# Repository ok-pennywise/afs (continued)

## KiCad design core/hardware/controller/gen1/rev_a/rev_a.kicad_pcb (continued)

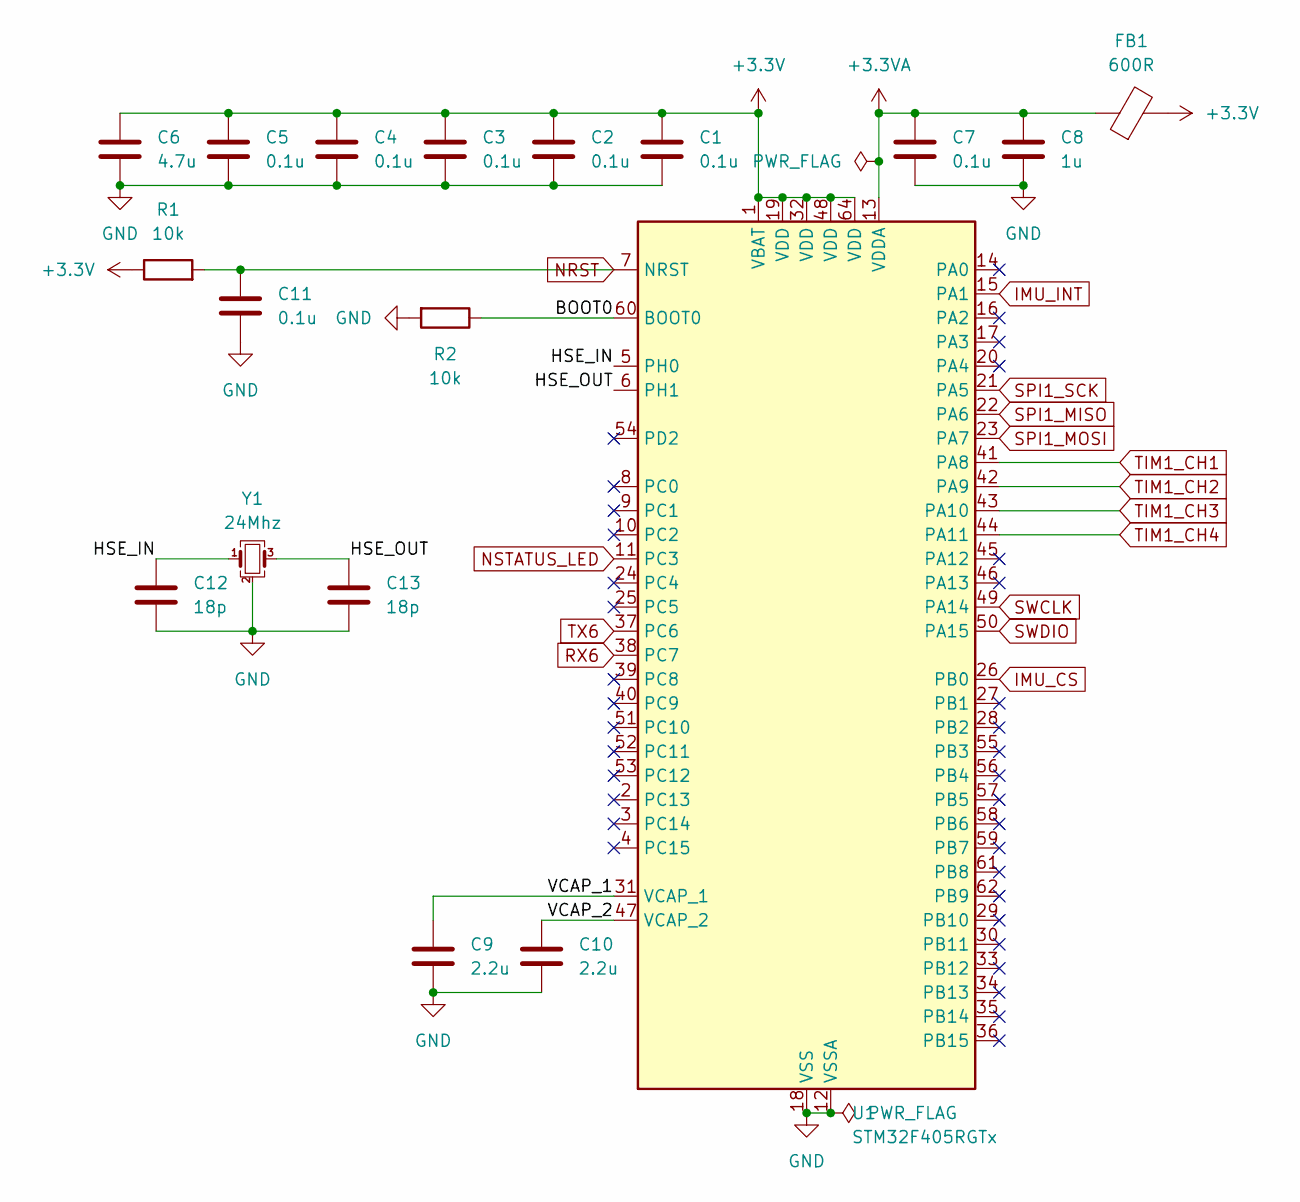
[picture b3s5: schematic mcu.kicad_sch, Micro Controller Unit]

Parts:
C1, C2, C3, C4, C5, C7, C11: 0.1u; C_0603_1608Metric_Pad1.08x0.95mm_HandSolder
C6: 4.7u; C_0603_1608Metric_Pad1.08x0.95mm_HandSolder
C8: 1u; C_0603_1608Metric_Pad1.08x0.95mm_HandSolder
C9, C10: 2.2u; C_0603_1608Metric_Pad1.08x0.95mm_HandSolder
C12, C13: 18p; C_0805_2012Metric_Pad1.18x1.45mm_HandSolder
FB1: 600R; L_0603_1608Metric_Pad1.05x0.95mm_HandSolder
R1, R2: 10k; R_0603_1608Metric_Pad0.98x0.95mm_HandSolder
U1: STM32F405RGTx; LQFP-64_10x10mm_P0.5mm
Y1: 24Mhz; Crystal_SMD_Abracon_ABM8G-4Pin_3.2x2.5mm

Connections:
+3.3V: C1.1, C2.1, C3.1, C4.1, C5.1, C6.1, FB1.2, R1.1, U1.1 (VBAT), U1.19 (VDD), U1.32 (VDD), U1.48 (VDD), U1.64 (VDD); also elsewhere on the board
+3.3VA: C7.1, C8.1, FB1.1, U1.13 (VDDA)
/MCU/BOOT0: R2.1, U1.60 (BOOT0)
/MCU/HSE_IN: C12.1, U1.5 (PH0), Y1.1
/MCU/HSE_OUT: C13.1, U1.6 (PH1), Y1.3
/MCU/VCAP_1: C9.1, U1.31 (VCAP_1)
/MCU/VCAP_2: C10.1, U1.47 (VCAP_2)
GND: C1.2, C2.2, C3.2, C4.2, C5.2, C6.2, C7.2, C8.2, C9.2, C10.2, C11.2, C12.2, C13.2, R2.2, U1.12 (VSSA), U1.18 (VSS), U1.63 (VSS), Y1.2 (G), Y1.4 (G); also elsewhere on the board
IMU_CS: U1.26 (PB0); also elsewhere on the board
IMU_INT: U1.15 (PA1); also elsewhere on the board
NRST: C11.1, R1.2, U1.7 (NRST); also elsewhere on the board
NSTATUS_LED: U1.11 (PC3); also elsewhere on the board
RX6: U1.38 (PC7); also elsewhere on the board
SPI1_MISO: U1.22 (PA6); also elsewhere on the board
SPI1_MOSI: U1.23 (PA7); also elsewhere on the board
SPI1_SCK: U1.21 (PA5); also elsewhere on the board
SWCLK: U1.49 (PA14); also elsewhere on the board
SWDIO: U1.50 (PA15); also elsewhere on the board
TIM1_CH1: U1.41 (PA8); also elsewhere on the board
TIM1_CH2: U1.42 (PA9); also elsewhere on the board
TIM1_CH3: U1.43 (PA10); also elsewhere on the board
TIM1_CH4: U1.44 (PA11); also elsewhere on the board
TX6: U1.37 (PC6); also elsewhere on the board

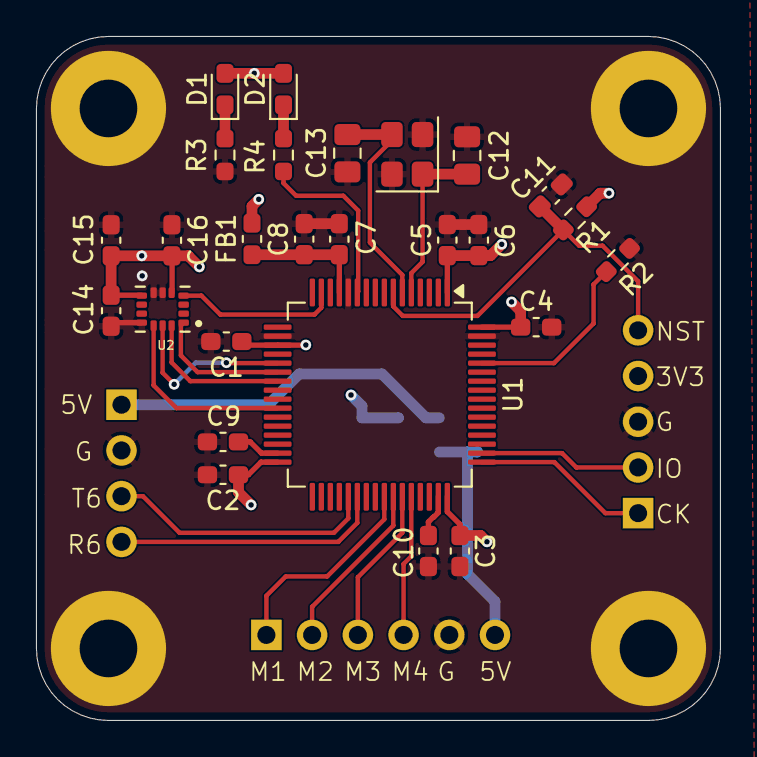
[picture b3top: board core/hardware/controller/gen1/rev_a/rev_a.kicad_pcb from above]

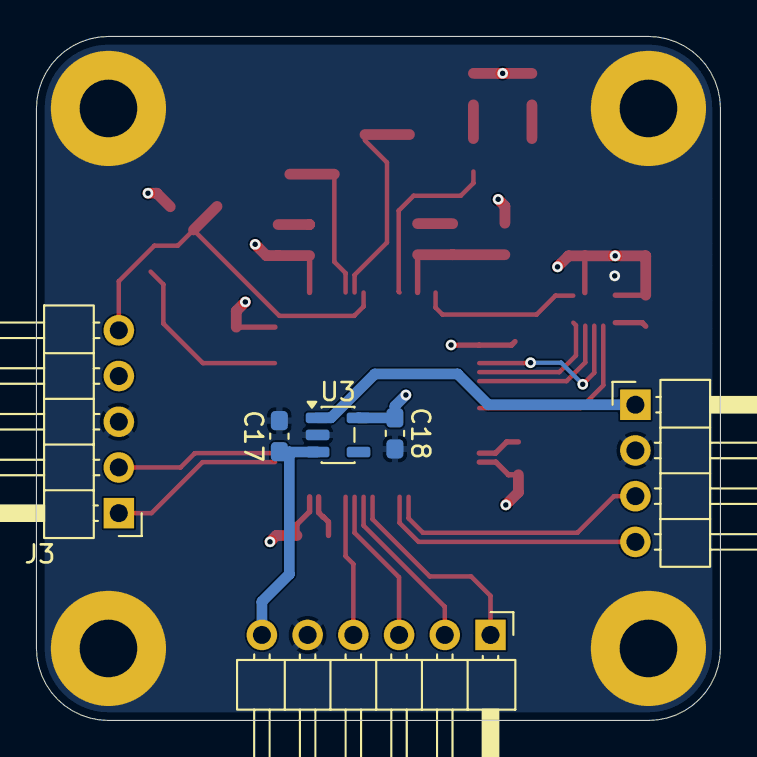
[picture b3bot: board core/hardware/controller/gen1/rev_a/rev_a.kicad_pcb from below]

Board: 4 copper layers, 38.0 x 38.0 mm, 36 parts (6 on the bottom side), 26 nets.

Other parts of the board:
H1, H2, H3, H4: MountingHole_Pad; MountingHole_3.2mm_M3_Pad

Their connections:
GND: H1.1 (1_1), H2.1 (1_1), H3.1 (1_1), H4.1 (1_1); also elsewhere on the board

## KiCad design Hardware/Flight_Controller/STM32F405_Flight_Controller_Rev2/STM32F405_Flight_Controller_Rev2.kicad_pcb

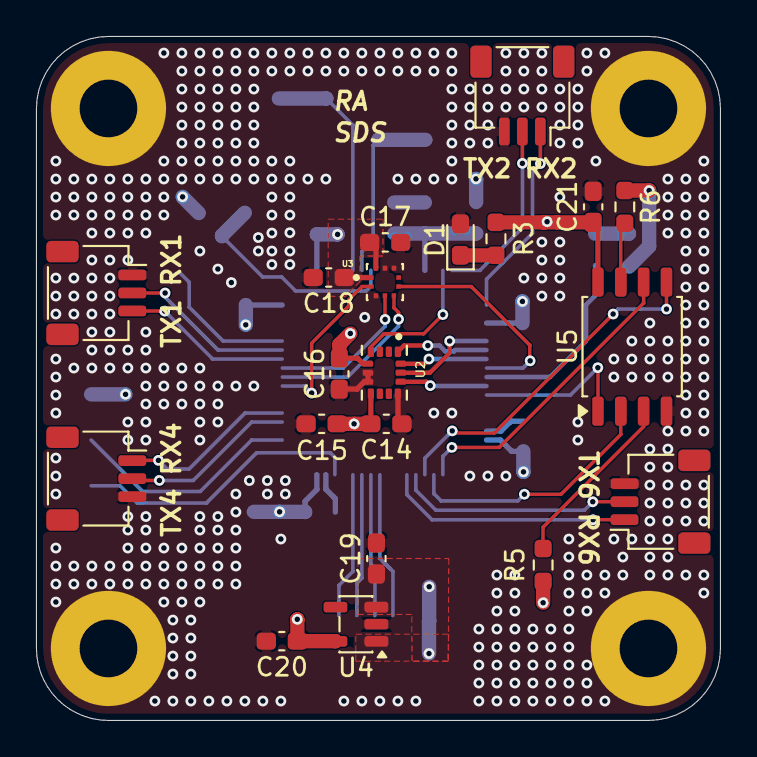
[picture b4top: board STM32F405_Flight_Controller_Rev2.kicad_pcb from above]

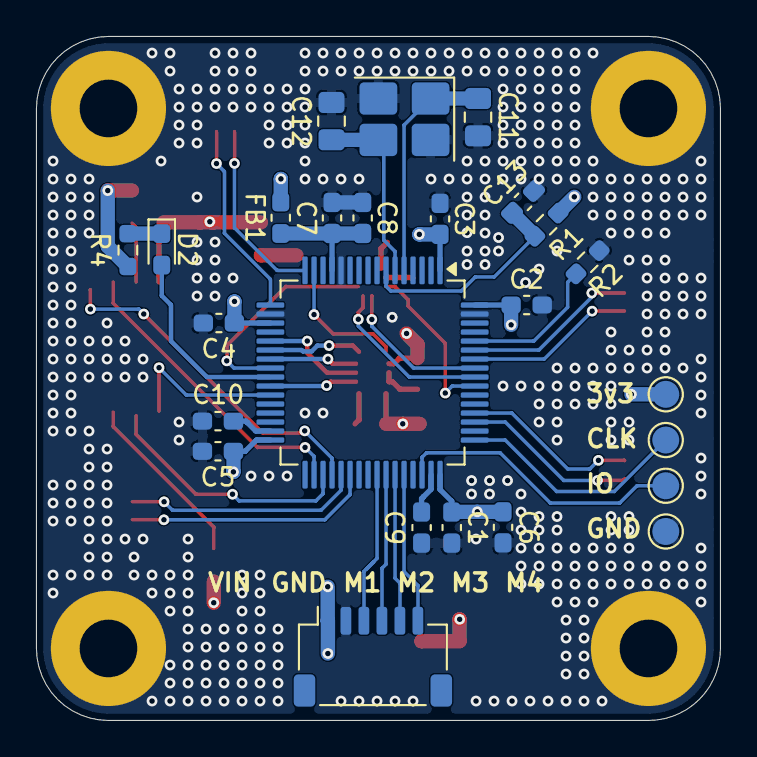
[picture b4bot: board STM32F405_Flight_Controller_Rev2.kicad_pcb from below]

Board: 4 copper layers, 38.0 x 38.0 mm, 49 parts (25 on the bottom side), 42 nets.

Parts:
C1, C2, C3, C4, C5, C7, C13, C14, C17, C18, C21: 0.1u; C_0603_1608Metric_Pad1.08x0.95mm_HandSolder
C6: 4.7u; C_0603_1608Metric_Pad1.08x0.95mm_HandSolder
C8, C19, C20: 1u; C_0603_1608Metric_Pad1.08x0.95mm_HandSolder
C9, C10, C15: 2.2u; C_0603_1608Metric_Pad1.08x0.95mm_HandSolder
C11, C12: 18p; C_0805_2012Metric_Pad1.18x1.45mm_HandSolder
C16: 10n; C_0603_1608Metric_Pad1.08x0.95mm_HandSolder
D1: RED; LED_0603_1608Metric_Pad1.05x0.95mm_HandSolder
D2: GREEN; LED_0603_1608Metric_Pad1.05x0.95mm_HandSolder
FB1: 600R; L_0603_1608Metric_Pad1.05x0.95mm_HandSolder
H1, H2, H3, H4: MountingHole_Pad; MountingHole_3.2mm_M3_Pad
J1: Conn_01x06_Socket; JST_SH_SM06B-SRSS-TB_1x06-1MP_P1.00mm_Horizontal
J2, J3, J4, J5: Conn_01x03_Socket; JST_SH_SM03B-SRSS-TB_1x03-1MP_P1.00mm_Horizontal
R1, R2, R5, R6: 10k; R_0603_1608Metric_Pad0.98x0.95mm_HandSolder
R3, R4: 330; R_0603_1608Metric_Pad0.98x0.95mm_HandSolder
TP1, TP2, TP3, TP4: TestPoint; TestPoint_Pad_D1.5mm
U1: STM32F405RGTx; LQFP-64_10x10mm_P0.5mm
U2: ICM-42688-P
U3: BMP390L
U4: AP2112K-3.3; SOT-23-5
U5: W25Q128JVS; SOIC-8_5.3x5.3mm_P1.27mm
Y1: Crystal; Crystal_SMD_3225-4Pin_3.2x2.5mm_HandSoldering

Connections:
+3.3V: C1.1, C2.1, C3.1, C4.1, C5.1, C6.1, C14.2, C15.2, C16.1, C17.1, C18.1, C20.1, C21.1, FB1.2, R1.1, R3.2, R4.2, R5.2, R6.1, TP1.1 (1_1), U1.1 (VBAT), U1.19 (VDD), U1.32 (VDD), U1.48 (VDD), U1.64 (VDD), U2.5 (VDDIO), U2.8 (VDD), U3.1 (VDDIO), U3.10 (VDD), U4.5 (VOUT), U5.8 (VCC)
+3.3VA: C7.1, C8.1, FB1.1, U1.13 (VDDA)
+5V: C19.1, J1.1, U4.1 (VIN), U4.3 (EN)
/MCU/BOOT0: R2.2, U1.60 (BOOT0)
/MCU/OSC_IN: C11.1, U1.5 (PH0), Y1.1
/MCU/OSC_OUT: C12.1, U1.6 (PH1), Y1.3
BARO_CS: U1.24 (PC4), U3.6 (~CS)
FLASH_CS: U1.27 (PB1), U5.1 (~CS)
GND: C1.2, C2.2, C3.2, C4.2, C5.2, C6.2, C7.2, C8.2, C9.2, C10.2, C11.2, C12.2, C13.2, C14.1, C15.1, C16.2, C17.2, C18.2, C19.2, C20.2, C21.2, D1.2 (A), H1.1 (1_1), H2.1 (1_1), H3.1 (1_1), H4.1 (1_1), J1.2, J2.1, J3.3, J4.3, J5.3, R2.1, TP4.1 (1_1), U1.12 (VSSA), U1.18 (VSS), U1.63 (VSS), U2.6 (GND), U2.7 (RESV_7), U2.11 (RESV_11), U3.3 (VSS/GND), U3.8 (VSS/GND), U3.9 (VSS/GND), U4.2 (GND), U5.4 (GND), Y1.2 (G), Y1.4 (G)
IMU_CS: U1.26 (PB0), U2.12 (AP_CS)
IMU_INT: U1.15 (PA1), U2.4 (INT1/INT)
NRST: C13.1, R1.2, U1.7 (NRST)
NSTATUS_LED: D2.2 (A), U1.25 (PC5)
unnamed: D1.1 (K), R3.1
unnamed: D2.1 (K), R4.1
unnamed: C10.1, U1.31 (VCAP_1)
unnamed: C9.1, U1.47 (VCAP_2)
unnamed: R6.2, U5.7 (~HOLD/~RESET/IO_{3})
unnamed: R5.1, U5.3 (~WP/IO_{2})
RX1: J2.2, U1.59 (PB7)
RX2: J4.1, U1.17 (PA3)
RX4: J5.1, U1.52 (PC11)
RX6: J3.1, U1.38 (PC7)
SPI1_MISO: U1.22 (PA6), U2.1 (AP_SDO/AP_AD0)
SPI1_MOSI: U1.23 (PA7), U2.14 (AP_SDA/AP_SDIO/AP_SDI)
SPI1_SCK: U1.21 (PA5), U2.13 (AP_SCL/AP_SCLK)
SPI2_MISO: U1.35 (PB14), U5.2 (DO/IO_{1})
SPI2_MOSI: U1.36 (PB15), U5.5 (DI/IO_{0})
SPI2_SCK: U1.34 (PB13), U5.6 (CLK)
SPI3_MISO: U1.56 (PB4), U3.5 (SDO/DNC/SA0)
SPI3_MOSI: U1.57 (PB5), U3.4 (SDI/SDO/SDA)
SPI3_SCK: U1.55 (PB3), U3.2 (SCK/SCL)
SWCLK: TP2.1 (1_1), U1.49 (PA14)
SWDIO: TP3.1 (1_1), U1.46 (PA13)
TIM1_CH1: J1.3, U1.41 (PA8)
TIM1_CH2: J1.4, U1.42 (PA9)
TIM1_CH3: J1.5, U1.43 (PA10)
TIM1_CH4: J1.6, U1.44 (PA11)
TX1: J2.3, U1.58 (PB6)
TX2: J4.2, U1.16 (PA2)
TX4: J5.2, U1.51 (PC10)
TX6: J3.2, U1.37 (PC6)

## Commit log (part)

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2026-06-25 Remove PCB design
2026-06-25 Remove PCB
2026-06-27 PCB start
2026-06-28 Update swd and uart connector placement
2026-06-29 Update uart and swd routing
2026-06-29 Solve DRC and stich using ViaS
2026-06-29 Update fc PCB routing and motor silkscreen
2026-06-30 Final
2026-06-30 Add debug leds
